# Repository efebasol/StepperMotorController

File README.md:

# StepperMotorController

Stepper motor driver system based on TMC5160A + STM32. Long-term goal: a 6-axis robot arm controller made of 1 power distribution board, 1 main control board and 6 driver boards.

## Board status

| Board | Folder | Revision | Stage |
|---|---|---|---|
| Power board | `hardware/power` | Rev A | Schematic complete (incl. EMI filter #65) · layout next |
| Driver board | `hardware/driver` | Rev A | Schematic |
| Firmware | `firmware` | – | Not started |

Tracking: [GitHub Project](https://github.com/users/efebasol/projects/12)

## Repository layout

```
hardware/
  power/     KiCad project – power board (48V in, brake chopper, 24V/5V buck, 12V/3V3 LDO, 24V eFuse) – see its README
  driver/    KiCad project – TMC5160 + MOSFET driver board
  lib/       Shared library: symbols/, footprints/, 3dmodels/
firmware/    STM32CubeIDE project
docs/        Calculations, decisions, notes
ci/          CI scripts (ERC/DRC, outputs, visual diff)
```

Libraries are resolved from inside the project (`${KIPRJMOD}/../lib/...`), so the project opens without broken parts on any machine.

> **Library rule:** don't leave parts linked to machine-local libraries (e.g. the KiCad PCM `PCM_JLCPCB-*` libs). Save them into `Step Motor Controller` (symbols/footprints) or use the standard `Device:R` / `Device:C` + an `LCSC` field. CI flags them as ERC warnings.

## Conventions

- **Commit messages:** `hw(power): ...`, `hw(driver): ...`, `fw(encoder): ...`, `docs: ...`, `ci: ...`
  Add `closes #NN` to close an issue from a commit.
- **Before committing:** save and close KiCad.
- **An ordered revision is frozen:** tag (`power-rev-a`) + GitHub Release (Gerber, BOM, CPL, schematic PDF). Later changes go to Rev B.
- **Branches:** hardware lives on `main`; experiments on `experiment/...`, firmware features on `feature/...`.
- Datasheets, tokens and key files are never committed.

## Issues & labels

- Templates: 🐞 Bug · ⚠️ Risk · 🛠️ Task (New issue).
- Labels: `hw` / `fw`, `power`, `schematic` / `layout`, `bug`, `risk`, `rev-a`.
- **`robot-arm-phase`** – deliberately deferred until the 6-axis arm; filter by this label when that phase starts.

## CI

- **Hardware CI** – on every push: ERC, DRC, schematic PDF, BOM, Gerber, CPL. Outputs are available as artifacts in the Actions tab.
  Once layout is done, set `STRICT: "1"` in `.github/workflows/hardware-ci.yml` → the run fails on errors.
- **Visual Diff** – before | after | diff images of changed schematics/PCBs. Can also be run manually against any tag/commit.

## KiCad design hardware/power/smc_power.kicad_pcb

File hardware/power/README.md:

# Power board

Rev A — single-motor bench prototype power board.
Feeds the driver board (48 V), the stepper motor brake (24 V) and the logic (5 V / 3V3).

## Blocks

| Block | Key parts | Notes |
|---|---|---|
| 48 V input | J2 XT60 → F1 fuse → D3 MBR10100 (reverse polarity) → R21 NTC MF72 5D13 (inrush, 5 Ω / 5 A) → **DM π filter C34 / L4 2.2 µH / C35** → +VM; D4 SMBJ51A TVS and C20/C21 470 µF bulk on +VM | EMI filter #65 (CMC dropped: no 10 A part in stock, noise is mostly DM). LM74700 ideal diode deferred (#60) |
| Brake chopper | IC1 LM393 + U6 TL431B (±0.3 %, REF–K via R36 0 Ω), Q1 AOD4126, U5 MCP1416 gate driver, R16 RX24 50 W 33 Ω (off-board, J1), D5 SS510 flyback | Turn-on 54.14–55.23 V, turn-off 52.27–53.32 V (0.1 % divider) → **PSU max ≤ 52 V**. Capacity ≈ 1.66 A |
| 12 V LDO | U7 L78L12 (fed from 24 V) | Gate-driver supply only, not on any connector |
| 24 V buck | U1 TPS54360, L1 68 µH | Brake rail. UVLO start ~34 V / stop ~32 V |
| 24 V brake eFuse | U4 TPS16630, R30 12k → I<sub>LIM</sub> ≈ 1.5 A, UVLO ≈ 20 V / OVP ≈ 30 V, auto-retry | D13 = fault LED (PGOOD low), FLT# → J5 pin 5 (firmware #66) |
| 5 V buck | U3 TPS54360, L2 22 µH, 2×22 µF X7R out (C16, C27), comp. R10 4.22k / C18 27 nF / C17 220 pF | UVLO start ~34 V / stop ~32 V |
| 3V3 LDO | U2 AP2112K-3.3 | **max ~200 mA** (SOT-23-5 thermal); bigger LDO deferred (#61) |
| VBUS sense | R22 100k / R23 3.9k + 100 nF | 48 V → 1.80 V, ~82 V → 3.08 V. Firmware scaling #63 |
| Indicators | D6–D11 rail LEDs (48V, VM, 24V, 12V, 5V, 3V3), ~1.5 mA each | Silkscreen label next to each LED (#44) |

Design calculations: [`docs/power-design-notes.md`](../../docs/power-design-notes.md)

## Connectors

Board-to-board by **cables** (no stacking / backplane).

| Ref | Part | Function | Pinout |
|---|---|---|---|
| J2 | XT60PW-M | 48 V IN | 1: +48V · 2: GND |
| J3 | XT30PW-F | 48 V OUT (driver) | 1: VM · 2: GND |
| J4 | JST B2P-VH | 24 V BRAKE | 1: +24V · 2: GND |
| J5 | JST B5B-XH-A | LOGIC (main board) | 1: GND · 2: +5V · 3: +3V3 · 4: VBUS_SENSE · 5: TPS16630_FLT# |
| J1 | KF128 5.08 mm | Brake resistor R16 (off-board) | – |

Main-board side: 1 kΩ series resistor at the MCU ADC pin for VBUS_SENSE; one pull-up for FLT# (open-drain, active-low).

## Stackup

4 layers, 1.6 mm, JLCPCB.

| Layer | Copper | Use |
|---|---|---|
| L1 (F.Cu) | 2 oz | Power |
| L2 (In1.Cu) | 1 oz | Solid GND plane — never split (buck switching loops sit on top of it) |
| L3 (In2.Cu) | 1 oz | Signal + GND fill (keep it solid: it is the return path for L4) |
| L4 (B.Cu) | 2 oz | Power + signal |

**48 V, 24 V and SW nodes are routed on the 2 oz outer layers only** (inner 1 oz layers can't carry or dissipate that current). Vias between L1 and L4 are fine — current flows in the plated barrel.

> Order note: JLC's inner-layer default is 0.5 oz — select **1 oz** explicitly.

## Net classes

Values sized with IPC-2221 for 2 oz outer copper, ΔT ≈ 20 °C. Empty cells inherit `Default`.

| Net class | Clearance | Track width | Via size | Via hole | Nets / notes |
|---|---|---|---|---|---|
| `PWR_48V` | **0.6 mm** | 2.5 mm | 1.0 mm | 0.5 mm | 48 V bus. Main 10 A path (input → output connector) as pour where possible (10 A on 2 oz needs ≥2.4 mm) |
| `SW_NODE` | **0.6 mm** | 1.0 mm | – | – | Buck switch nodes (`SW_24V`, `SW_5V`, pattern `*SW_*`). Swing 0–48 V → 48 V clearance. Keep copper area minimal |
| `BOOT_NODE` | **0.6 mm** | 0.4 mm | – | – | Bootstrap nodes (`BOOT_24V`, `BOOT_5V`, pattern `*BOOT_*`). Rides on SW (up to ~SW + 8 V) → 48 V clearance, low current |
| `PWR_24V` | 0.25 mm | 0.8 mm | 0.8 mm | 0.4 mm | 24 V brake rail (motor brakes). Buck max 3 A → ≥0.45 mm |
| `PWR_5V` | 0.2 mm | 0.5 mm | 0.6 mm | 0.3 mm | 5 V logic rail; also `+12V` (L78L12 → MCP1416 gate driver, low current) |
| `PWR_3V3` | 0.2 mm | 0.4 mm | 0.6 mm | 0.3 mm | 3V3 LDO output |
| `GND` | 0.2 mm | 0.5 mm | 0.6 mm | 0.3 mm | Mostly planes/pours; tracks only for short links |
| `Default` | 0.2 mm | 0.25 mm | 0.6 mm | 0.3 mm | Signals (FB, comparator, gate drive, …) |

**FB nets** (`FB_24V`, `FB_5V`) stay in `Default` on purpose — see layout notes below.

Why 0.6 mm: IPC-2221 B2 (external, uncoated, 31–100 V). Between two classes KiCad applies the larger clearance, so every net next to 48 V automatically gets 0.6 mm.

Rules of thumb:
- ~1 A per 0.3 mm via → parallel vias on high-current transitions.
- Track width is the default, not a limit — widen freely, never go narrower.

### Layout notes

- **FB:** no net class needed — tiny current, width doesn't matter. What matters is placement: divider resistors right at the FB pin, short trace, never under or next to the SW node. A noisy FB makes the regulator output jitter.

### Global constraints (Board Setup → Constraints)

| Constraint | Value | Why |
|---|---|---|
| Min clearance | 0.15 mm | JLC 2 oz outer minimum |
| Min track width | 0.15 mm | JLC 2 oz outer minimum |
| Min via hole | 0.3 mm | |
| Min annular ring | 0.15 mm | |
| Copper to board edge | 0.5 mm | |

### Custom DRC rule (Board Setup → Custom Rules)

```
(version 1)
(rule "High-power nets: outer 2 oz layers only"
  (layer inner)
  (condition "A.NetClass == 'PWR_48V' || A.NetClass == 'PWR_24V' || A.NetClass == 'SW_NODE'")
  (constraint disallow track zone))
```

## Tracking

Issues: label `power` · Project: https://github.com/users/efebasol/projects/12

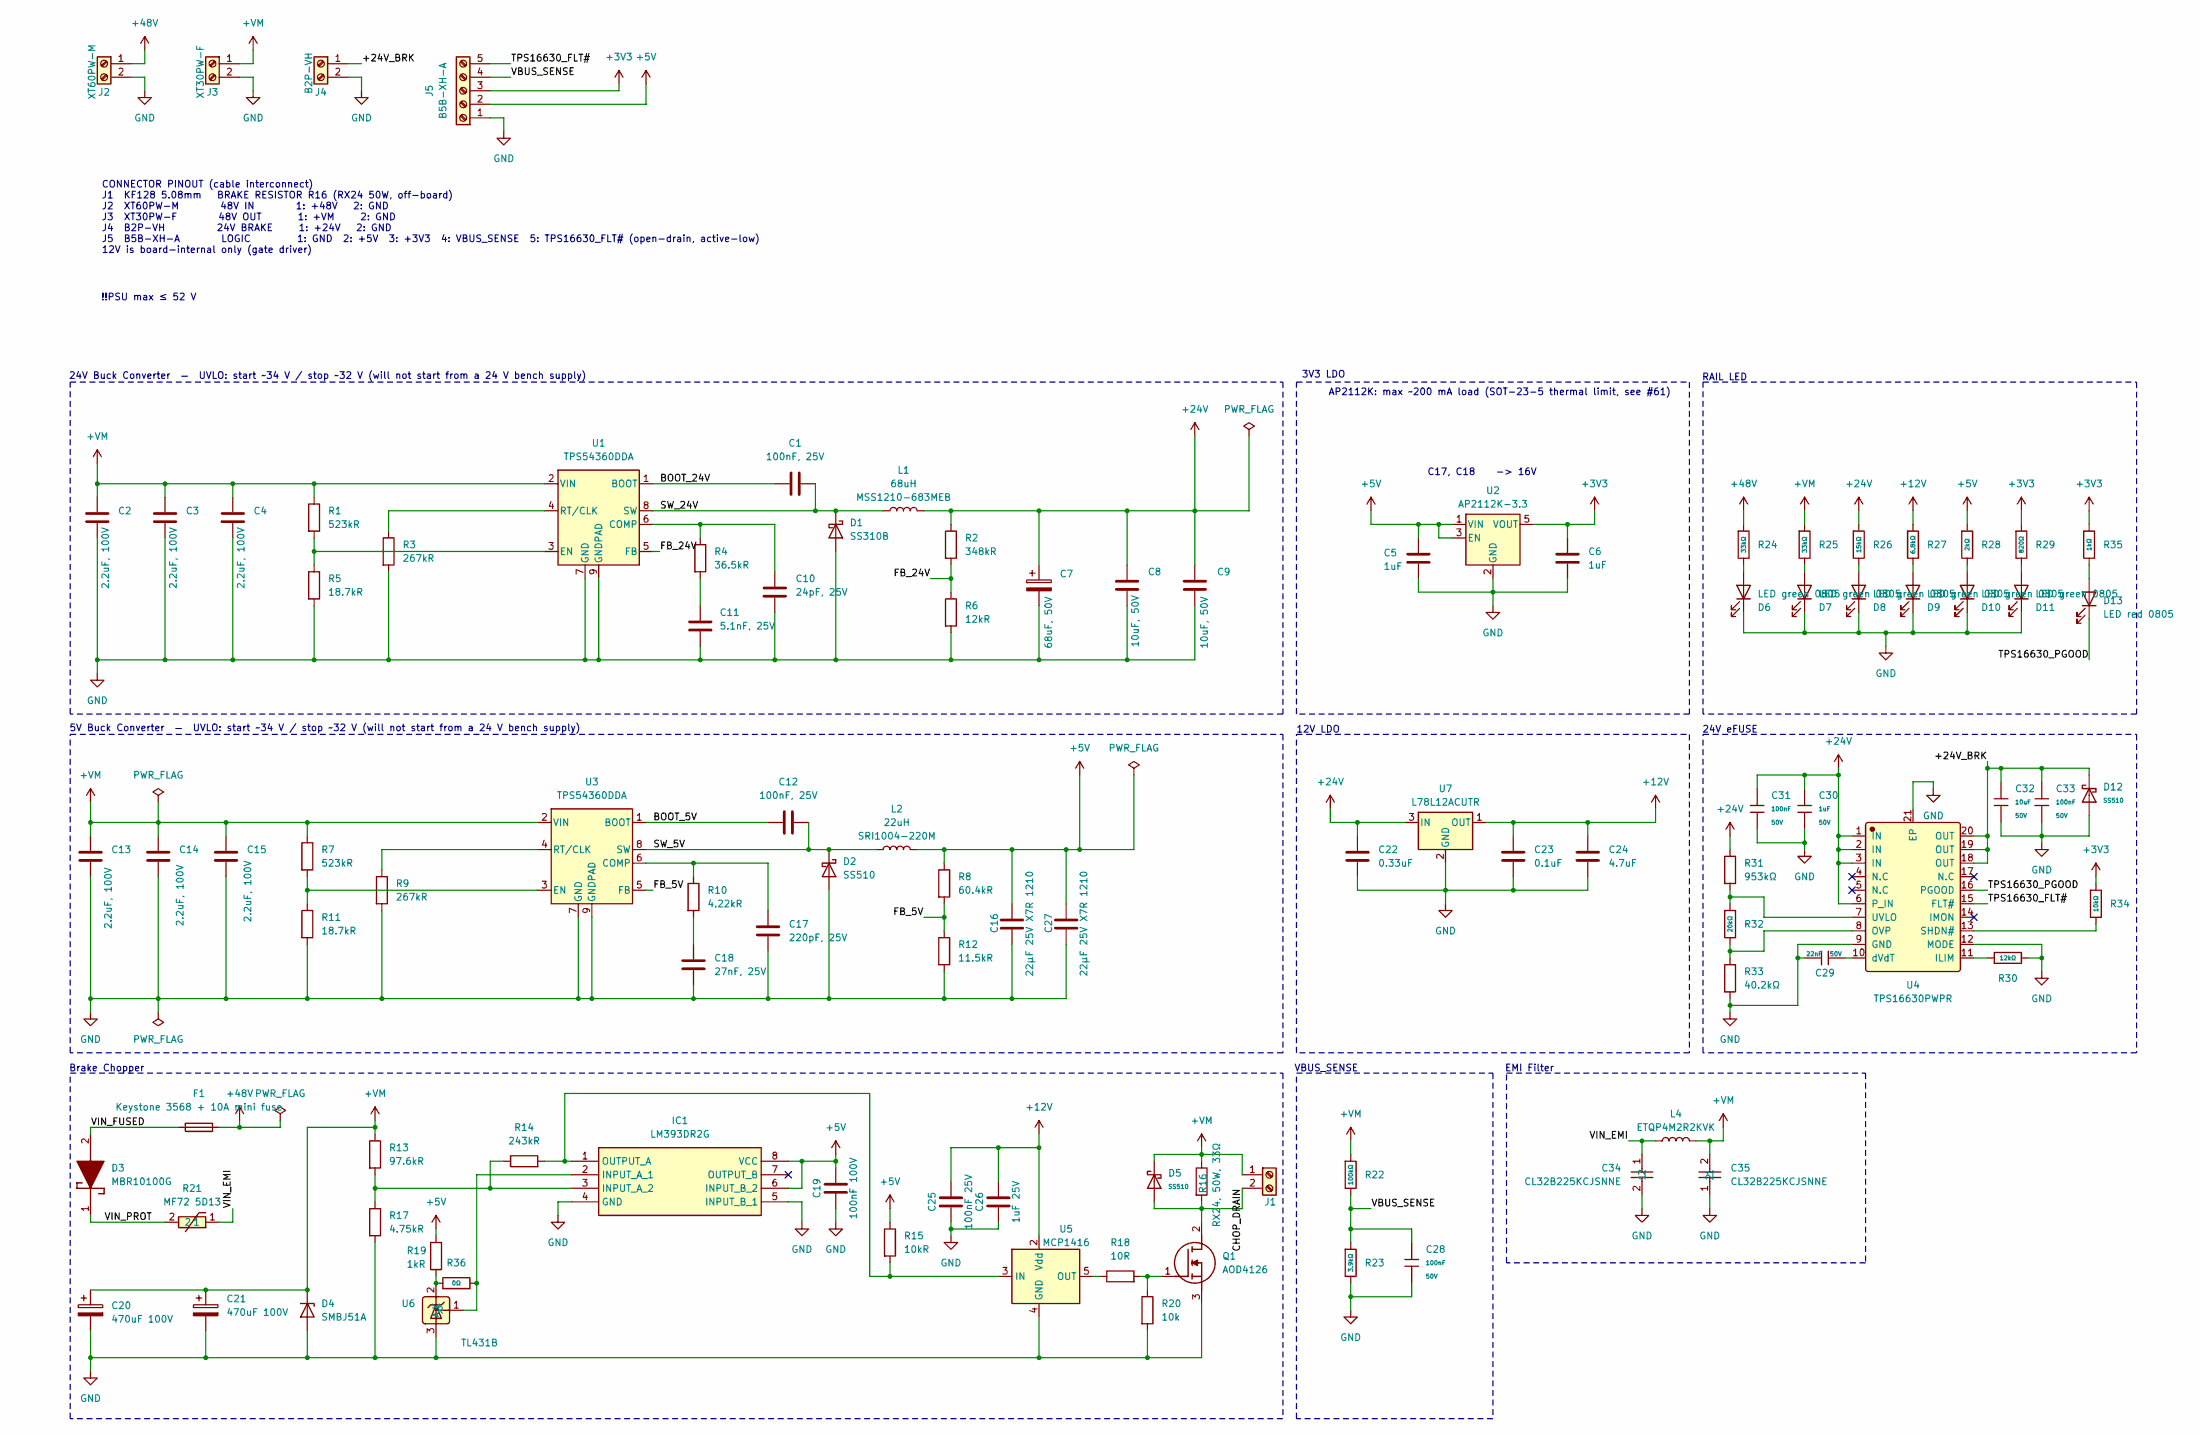
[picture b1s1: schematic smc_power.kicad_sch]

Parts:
C1, C12: 100nF, 25V; C_0805_2012Metric_Pad1.18x1.45mm_HandSolder; LCSC C49678
C2, C3, C4, C13, C14, C15: 2.2uF, 100V; C_1206_3216Metric_Pad1.33x1.80mm_HandSolder; LCSC C577211
C5, C6: 1uF; C_0805_2012Metric_Pad1.18x1.45mm_HandSolder; LCSC C28323
C7: 68uF, 50V; CP_Radial_D8.0mm_P3.50mm; LCSC C724604
C8, C9: 10uF, 50V; C_1206_3216Metric_Pad1.33x1.80mm_HandSolder; LCSC C5449000
C10: 24pF, 25V; C_0805_2012Metric_Pad1.18x1.45mm_HandSolder; LCSC C113827
C11: 5.1nF, 25V; C_0805_2012Metric_Pad1.18x1.45mm_HandSolder; LCSC C1750
C16, C27: 22µF 25V X7R 1210; C_1210_3225Metric_Pad1.33x2.70mm_HandSolder; LCSC C5341638
C17: 220pF, 25V; C_0805_2012Metric_Pad1.18x1.45mm_HandSolder; LCSC C107112
C18: 27nF, 25V; C_0805_2012Metric_Pad1.18x1.45mm_HandSolder; LCSC C376967
C19: 100nF 100V; C_0805_2012Metric_Pad1.18x1.45mm_HandSolder; LCSC C106243
C20, C21: 470uF 100V; CP_Radial_D16.0mm_P7.50mm; LCSC C49256827
C22: 0.33uF; C_0805_2012Metric_Pad1.18x1.45mm_HandSolder; LCSC C309049
C23: 0.1uF; C_0805_2012Metric_Pad1.18x1.45mm_HandSolder; LCSC C49678
C24: 4.7uF; C_0805_2012Metric_Pad1.18x1.45mm_HandSolder; LCSC C354262
C25: 100nF 25V; C_0805_2012Metric_Pad1.18x1.45mm_HandSolder; LCSC C49678
C26: 1uF 25V; C_0805_2012Metric_Pad1.18x1.45mm_HandSolder; LCSC C28323
C28, C31, C33: 100nF; C_0805_2012Metric_Pad1.18x1.45mm_HandSolder; Voltage Rated 50V; Tolerance ±10%; Part CC0805KRX7R9BB104; LCSC C49678
C29: 22nF; C_0805_2012Metric_Pad1.18x1.45mm_HandSolder; Voltage Rated 50V; Tolerance ±10%; Part CL21B223KBANNNC; LCSC C1729
C30: 1uF; C_0805_2012Metric_Pad1.18x1.45mm_HandSolder; Voltage Rated 50V; Tolerance ±10%; Part CL21B105KBFNNNE; LCSC C28323
C32: 10uF; C_0805_2012Metric_Pad1.18x1.45mm_HandSolder; Voltage Rated 50V; Tolerance ±10%; Part GRM21BR61H106KE43L; LCSC C440198
C34, C35: CL32B225KCJSNNE; C_1210_3225Metric; Manufacturer Part CL32B225KCJSNNE; LCSC C55151
D1: SS310B; D_SMB-SMC_Universal_Handsoldering; LCSC C14281
D2: SS510; D_SMA; LCSC C18199171
D3: MBR10100G; TO508P482X997X1956-2P; Manufacturer_Part_Number MBR10100; Mouser Part Number 863-MBR10100
D4: SMBJ51A; D_SMA-SMB_Universal_Handsoldering; LCSC C284023
D5, D12: SS510; D_SMA; Forward Voltage (Vf@If) 850mV@5A; Reverse Voltage (Vr) 100V; Part SS510; LCSC C18199171
D6, D7, D8, D9, D10, D11: LED green 0805; LED_0805_2012Metric_Pad1.15x1.40mm_HandSolder; LCSC C2297
D13: LED red 0805; LED_0805_2012Metric_Pad1.15x1.40mm_HandSolder; LCSC C84256
F1: Keystone 3568 + 10A mini fuse; Fuseholder_Blade_Mini_Keystone_3568
IC1: LM393DR2G; SOIC127P600X175-8N; Manufacturer_Part_Number LM393DR2GH; Mouser Part Number 863-LM393DR2GH
J1: KF128-5.08-2P; TerminalBlock_Phoenix_MKDS-1,5-2-5.08_1x02_P5.08mm_Horizont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; LCSC C474952
J2: XT60PW-M; AMASS_XT60PW-M_1x02_P7.20mm_Horizontal; LCSC C98732
J3: XT30PW-F; AMASS_XT30PW-F_1x02_P2.50mm_Horizontal; LCSC C2913282
J4: B2P-VH; JST_VH_B2P-VH_1x02_P3.96mm_Vertical; LCSC C160315
J5: B5B-XH-A; JST_XH_B5B-XH-A_1x05_P2.50mm_Vertical; LCSC C157991
L1: 68uH; L_SXN_SMDRI125; LCSC C5183009
L2: 22uH; L_Chilisin_BMRF00101040; LCSC C5174472
L4: ETQP4M2R2KVK; L_Panasonic_PCC-M0850M; LCSC C230663
Q1: AOD4126; AOD4185; Manufacturer_Part_Number AOD4126; LCSC C457934
R1, R7: 523kR; R_0805_2012Metric_Pad1.20x1.40mm_HandSolder; LCSC C228890
R2: 348kR; R_0805_2012Metric_Pad1.20x1.40mm_HandSolder; LCSC C400703
R3, R9: 267kR; R_0805_2012Metric_Pad1.20x1.40mm_HandSolder; LCSC C104164
R4: 36.5kR; R_0805_2012Metric_Pad1.20x1.40mm_HandSolder; LCSC C2999585
R5, R11: 18.7kR; R_0805_2012Metric_Pad1.20x1.40mm_HandSolder; LCSC C17499
R6: 12kR; R_0805_2012Metric_Pad1.20x1.40mm_HandSolder; LCSC C17444
R8: 60.4kR; R_0805_2012Metric_Pad1.20x1.40mm_HandSolder; LCSC C2933477
R10: 4.22kR; R_0805_2012Metric_Pad1.20x1.40mm_HandSolder; LCSC C2933442
R12: 11.5kR; R_0805_2012Metric_Pad1.20x1.40mm_HandSolder; LCSC C17418
R13: 97.6kR; R_0805_2012Metric_Pad1.20x1.40mm_HandSolder; Tolerance 0.1%; LCSC C5266156
R14: 243kR; R_0805_2012Metric_Pad1.20x1.40mm_HandSolder; Tolerance 1%; LCSC C2930186
R15: 10kR; R_0805_2012Metric_Pad1.20x1.40mm_HandSolder; LCSC C17414
R16: RX24, 50W, 33Ω
R17: 4.75kR; R_0805_2012Metric_Pad1.20x1.40mm_HandSolder; Tolerance 0.1%; LCSC C2692699
R18: 10R; R_0805_2012Metric_Pad1.20x1.40mm_HandSolder; LCSC C17415
R19: 1kR; R_0805_2012Metric_Pad1.20x1.40mm_HandSolder; LCSC C17513
R20: 10k; R_0805_2012Metric_Pad1.20x1.40mm_HandSolder; LCSC C17414
R21: MF72 5D13; NTC_Disc_D13mm_W5.5mm_P7.5mm; Manufacturer Part MF72 5D13; LCSC C72683
R22: 100kΩ; R_0805_2012Metric_Pad1.20x1.40mm_HandSolder; Overload Voltage (Max) 150V; Tolerance ±1%; Part 0805W8F1003T5E; LCSC C149504
R23: 3.9kΩ; R_0805_2012Metric_Pad1.20x1.40mm_HandSolder; Overload Voltage (Max) 150V; Tolerance ±1%; Part 0805W8F3901T5E; LCSC C17614
R24, R25: 33kΩ; R_0805_2012Metric_Pad1.20x1.40mm_HandSolder; Overload Voltage (Max) 150V; Tolerance ±1%; Part 0805W8F3302T5E; LCSC C17633
R26: 15kΩ; R_0805_2012Metric_Pad1.20x1.40mm_HandSolder; Overload Voltage (Max) 150V; Tolerance ±1%; Part 0805W8F1502T5E; LCSC C17475
R27: 6.8kΩ; R_0805_2012Metric_Pad1.20x1.40mm_HandSolder; Overload Voltage (Max) 150V; Tolerance ±1%; Part 0805W8F6801T5E; LCSC C17772
R28: 2kΩ; R_0805_2012Metric_Pad1.20x1.40mm_HandSolder; Overload Voltage (Max) 150V; Tolerance ±1%; Part 0805W8F2001T5E; LCSC C17604
R29: 820Ω; R_0805_2012Metric_Pad1.20x1.40mm_HandSolder; Overload Voltage (Max) 150V; Tolerance ±1%; Part 0805W8F8200T5E; LCSC C17837
R30: 12kΩ; R_0805_2012Metric_Pad1.20x1.40mm_HandSolder; Overload Voltage (Max) 150V; Tolerance ±1%; Part 0805W8F1202T5E; LCSC C17444
R31: 953kΩ; R_0805_2012Metric_Pad1.20x1.40mm_HandSolder; LCSC C3013231
R32: 20kΩ; R_0805_2012Metric_Pad1.20x1.40mm_HandSolder; Overload Voltage (Max) 150V; Tolerance ±1%; Part 0805W8F2002T5E; LCSC C4328
R33: 40.2kΩ; R_0805_2012Metric_Pad1.20x1.40mm_HandSolder; LCSC C2933438
R34: 10kΩ; R_0805_2012Metric_Pad1.20x1.40mm_HandSolder; Overload Voltage (Max) 150V; Tolerance ±1%; Part 0805W8F1002T5E; LCSC C17414
R35: 1kΩ; R_0805_2012Metric_Pad1.20x1.40mm_HandSolder; Overload Voltage (Max) 150V; Tolerance ±1%; Part 0805W8F1001T5E; LCSC C17513
R36: 0Ω; R_0805_2012Metric_Pad1.20x1.40mm_HandSolder; Overload Voltage (Max) 150V; Tolerance ±1%; Part 0805W8F0000T5E; LCSC C17477
U1, U3: TPS54360DDA; TI_SO-PowerPAD-8_ThermalVias; LCSC C44377
U2: AP2112K-3.3; SOT-23-5; LCSC C51118
U4: TPS16630PWPR; HTSSOP-20-1EP_4.4x6.5mm_P0.65mm_EP2.85x4mm; Manufacturer Part TPS16630PWPR; LCSC C1849461
U5: MCP1416; SOT-23-5; LCSC C83775
U6: TL431B; SOT-23-3; Manufacturer Part TL431B; LCSC C54830630
U7: L78L12ACUTR; SOT-89-3; LCSC C69601

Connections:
+3V3: C6.1, J5.3, R29.1, R34.1, R35.1, U2.5 (VOUT)
+5V: C5.1, C16.1, C19.2, C27.1, IC1.6 (INPUT_B_2), IC1.8 (VCC), J5.2, L2.2, R8.1, R15.1, R19.2, R28.1, U2.1 (VIN), U2.3 (EN)
+12V: C23.1, C24.1, C25.2, C26.2, R27.1, U5.2 (Vdd), U7.1 (OUT)
+24V: C7.1, C8.1, C9.1, C22.1, C30.1, C31.1, L1.2, R2.1, R26.1, R31.1, U4.1 (IN), U4.2 (IN), U4.3 (IN), U4.6 (P_IN), U7.3 (IN)
+48V: F1.2, J2.1, R24.1
+VM: C2.1, C3.1, C4.1, C13.1, C14.1, C15.1, C20.1, C21.1, C35.2, D4.1 (K), D5.1, J1.1, J3.1, L4.2, R1.1, R7.1, R13.1, R16.1, R22.1, R25.1, U1.2 (VIN), U3.2 (VIN)
/+24V_BRK: C32.1, C33.1, D12.1, J4.1, U4.18 (OUT), U4.19 (OUT), U4.20 (OUT)
/BOOT_5V: C12.1, U3.1 (BOOT)
/BOOT_24V: C1.1, U1.1 (BOOT)
/CHOP_DRAIN: D5.2, J1.2, Q1.2 (D), R16.2
/FB_5V: R8.2, R12.1, U3.5 (FB)
/FB_24V: R2.2, R6.1, U1.5 (FB)
/SW_5V: C12.2, D2.1 (K), L2.1, U3.8 (SW)
/SW_24V: C1.2, D1.1 (K), L1.1, U1.8 (SW)
/TPS16630_FLT#: J5.5, U4.15 (FLT#)
/TPS16630_PGOOD: D13.1 (K), U4.16 (PGOOD)
/VBUS_SENSE: C28.1, J5.4, R22.2, R23.1
/VIN_EMI: C34.1, L4.1, R21.1
/VIN_FUSED: D3.2 (A), F1.1
/VIN_PROT: D3.1 (K), R21.2
GND: C2.2, C3.2, C4.2, C5.2, C6.2, C7.2, C8.2, C9.2, C10.2, C11.2, C13.2, C14.2, C15.2, C16.2, C17.2, C18.2, C19.1, C20.2, C21.2, C22.2, C23.2, C24.2, C25.1, C26.1, C27.2, C28.2, C29.1, C30.2, C31.2, C32.2, C33.2, C34.2, C35.1, D1.2 (A), D2.2 (A), D4.2 (A), D6.1 (K), D7.1 (K), D8.1 (K), D9.1 (K), D10.1 (K), D11.1 (K), D12.2, IC1.4 (GND), IC1.5 (INPUT_B_1), J2.2, J3.2, J4.2, J5.1, Q1.3 (S), R3.2, R5.2, R6.2, R9.2, R11.2, R12.2, R17.2, R20.2, R23.2, R30.2, R33.2, U1.7 (GND), U1.9 (GNDPAD), U2.2 (GND), U3.7 (GND), U3.9 (GNDPAD), U4.9 (GND), U4.12 (MODE), U4.21 (EP), U5.4 (GND), U6.3 (A), U7.2 (GND)
unnamed: C11.1, R4.2
unnamed: C18.1, R10.2
unnamed: D6.2 (A), R24.2
unnamed: D7.2 (A), R25.2
unnamed: D8.2 (A), R26.2
unnamed: D9.2 (A), R27.2
unnamed: D10.2 (A), R28.2
unnamed: D11.2 (A), R29.2
unnamed: D13.2 (A), R35.2
unnamed: IC1.2 (INPUT_A_1), R36.2, U6.1 (R)
unnamed: IC1.3 (INPUT_A_2), R13.2, R14.1, R17.1
unnamed: IC1.1 (OUTPUT_A), R14.2, R15.2, U5.3 (IN)
unnamed: Q1.1 (G), R18.2, R20.1
unnamed: C10.1, R4.1, U1.6 (COMP)
unnamed: R1.2, R5.1, U1.3 (EN)
unnamed: R3.1, U1.4 (RT/CLK)
unnamed: C17.1, R10.1, U3.6 (COMP)
unnamed: R7.2, R11.1, U3.3 (EN)
unnamed: R9.1, U3.4 (RT/CLK)
unnamed: R30.1, U4.11 (ILIM)
unnamed: R32.2, R33.1, U4.8 (OVP)
unnamed: R34.2, U4.13 (SHDN#)
unnamed: R31.2, R32.1, U4.7 (UVLO)
unnamed: C29.2, U4.10 (dVdT)
unnamed: R18.1, U5.5 (OUT)
unnamed: R19.1, R36.1, U6.2 (K)

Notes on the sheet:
Brake Chopper
5V Buck Converter — UVLO: start ~34 V / stop ~32 V (will not start from a 24 V bench supply)
3V3 LDO
C17, C18 -> 16V
24V eFUSE
EMI Filter
!!PSU max ≤ 52 V
VBUS_SENSE
AP2112K: max ~200 mA load (SOT-23-5 thermal limit, see #61)
24V Buck Converter — UVLO: start ~34 V / stop ~32 V (will not start from a 24 V bench supply)
CONNECTOR PINOUT (cable interconnect) J1 KF128 5.08mm BRAKE RESISTOR R16 (RX24 50W, off-board) J2 XT60PW-M 48V IN 1: +48V 2: GND J3 XT30PW-F 48V OUT 1: +VM 2: GND J4 B2P-VH 24V BRAKE 1: +24V 2: GND J5 B5B-XH-A LOGIC 1: GND 2: +5V 3: +3V3 4: VBUS_SENSE 5: TPS16630_FLT# (open-drain, active-low) 12V i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
12V LDO
RAIL LED

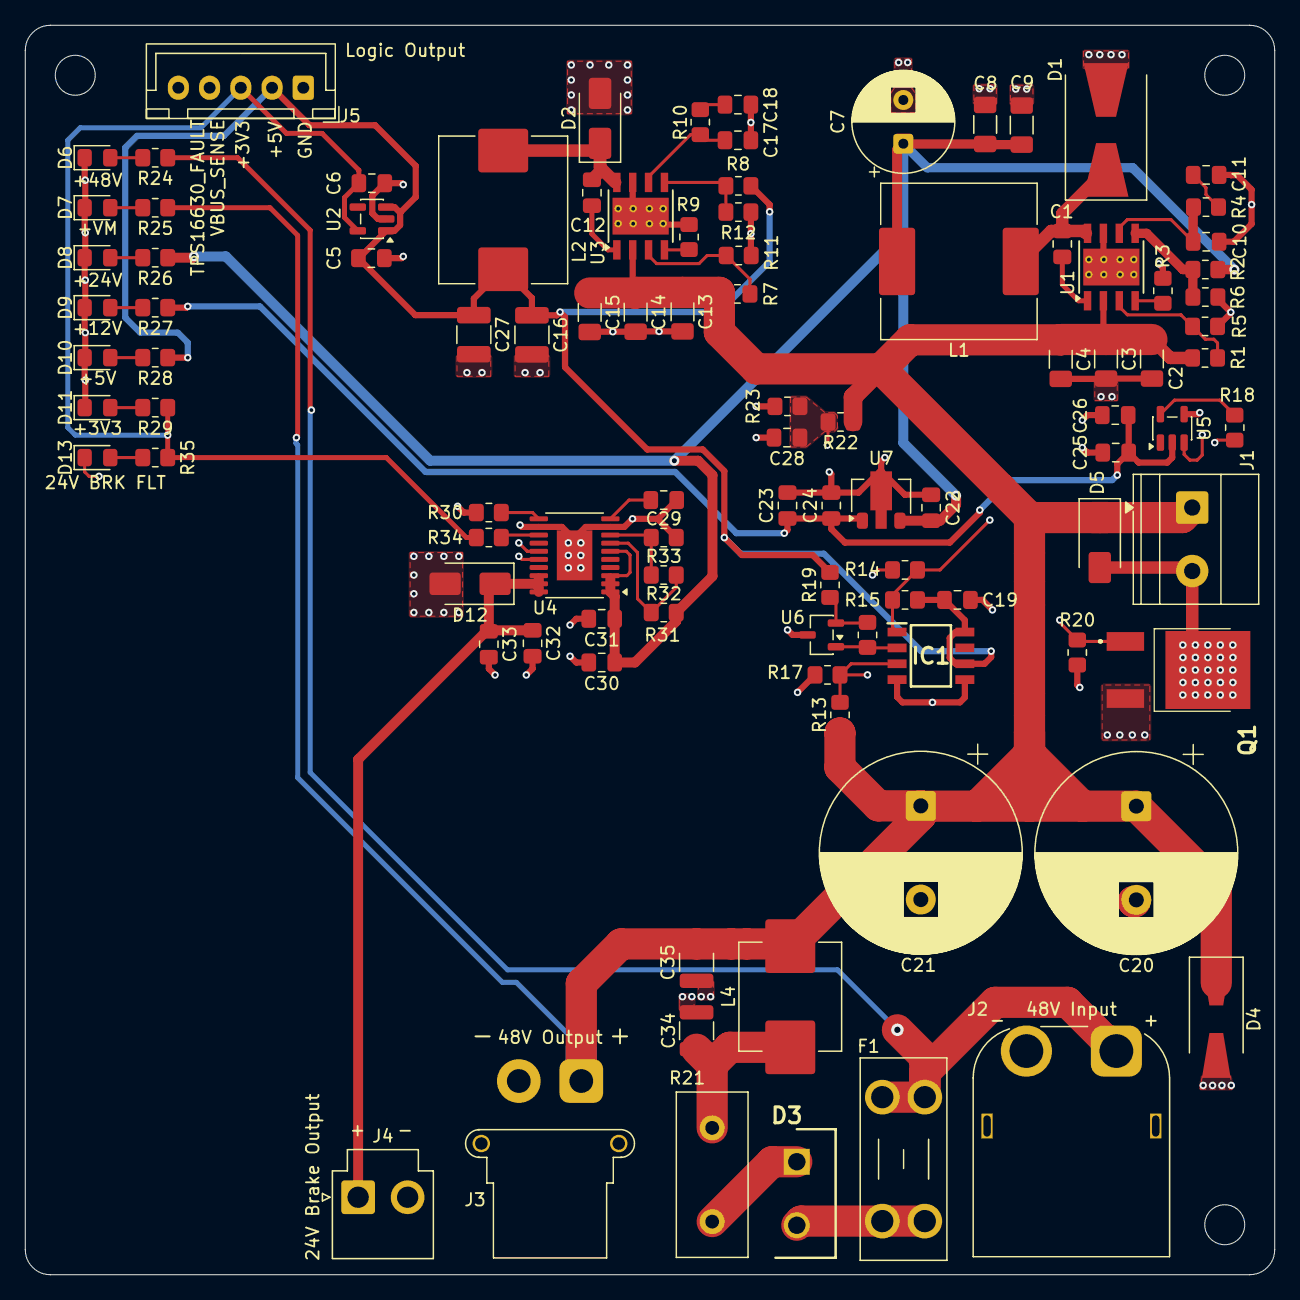
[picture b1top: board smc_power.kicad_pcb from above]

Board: 4 copper layers, 100.0 x 100.0 mm, 104 parts (0 on the bottom side), 47 nets.

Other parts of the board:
H1, H2, H3: MountingHole_M3; MountingHole_3.2mm_M3
